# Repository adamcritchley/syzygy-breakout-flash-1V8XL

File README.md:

# Double-Wide SYZYGY Breakout Flash
SYZYGY 56 pin Breakout Board that uses smart VIO to support any voltage flash chip. I wanted a way to experiment with flash without having to spin a new board for each footprint or solder yet another BGA or TSOP. Flash programmers with ZIF adapters seemed like the best choice and SYZYGY would make it compatible with a wide range of FPGA boards. This is the biggest and baddest version of the other SYZYGY flash breakout boards and requires the smart VIO in the SYZYGY DNA to be set to your flash logic level. It requires two adjacent standard ports which can only be found on a handful of FPGA dev boards such as the [Opal Kelly XEM8320](https://opalkelly.com/products/xem8320/).

# Building Firmware
A prebuilt firmware has been provided in the 'firmware' directory. If you want to customize the SMART VIO then modify 'szg-flash-std.json' with the custom power values and use the official [SYZYGY tools](https://github.com/SYZYGYfpga/syzygy-tools/) repo to build the firmware. 

```bash
python ..\..\syzygy-tools\dna-tools\syzygy-tools.py -d ..\szg-dna\SZG-FLASH\szg-flash-std.json -f ..\..\syzygy-tools\pod-fw\avr-dna-fw-main.hex
```

# Fabrication
I used JLCPCB with 1oz inner and outer copper weight and the standard JLC041611-7628 impedance control.

# FPGA Development
The board has silkscreen pin designators for the Opal Kelly XEM8320. Theoretically you can use this board with any FPGA dev board that has a double-wide SYZYGY connector along with the respective controller for your flash device OR find someway to expose it to AXI and PS to use it with flashrom. As I figure out specific tools that work well then I'll update this README with tutorials.

# BOM
You can find datasheets for each component in the datasheets directory. All of the components can be bought from Mouser or Digikey. 
* Epson SG5032VAN (up to 100 MHz)
* Texas Instrument TLV1117LV
* Aries 48-6554-11
* KF2510 8-pin Vertical Connector

# Future Work
This board design is complete and tested with the Opal Kelly XEM8320. As I find/create IP and software that works with this board then I'll update this README with tutorials on how to use them. Feel free to create a GitHub issue detailing your own success story or use case.

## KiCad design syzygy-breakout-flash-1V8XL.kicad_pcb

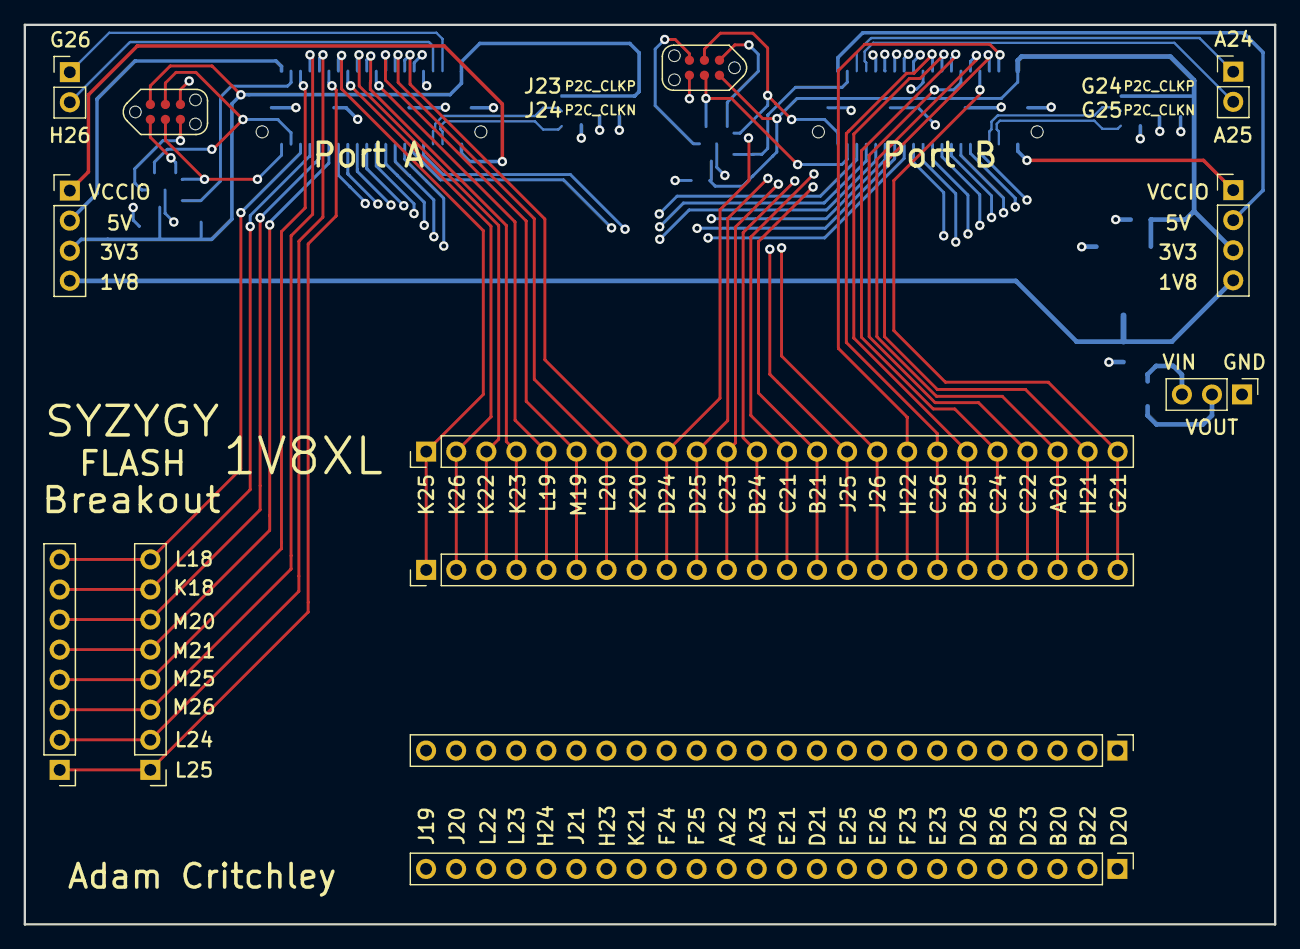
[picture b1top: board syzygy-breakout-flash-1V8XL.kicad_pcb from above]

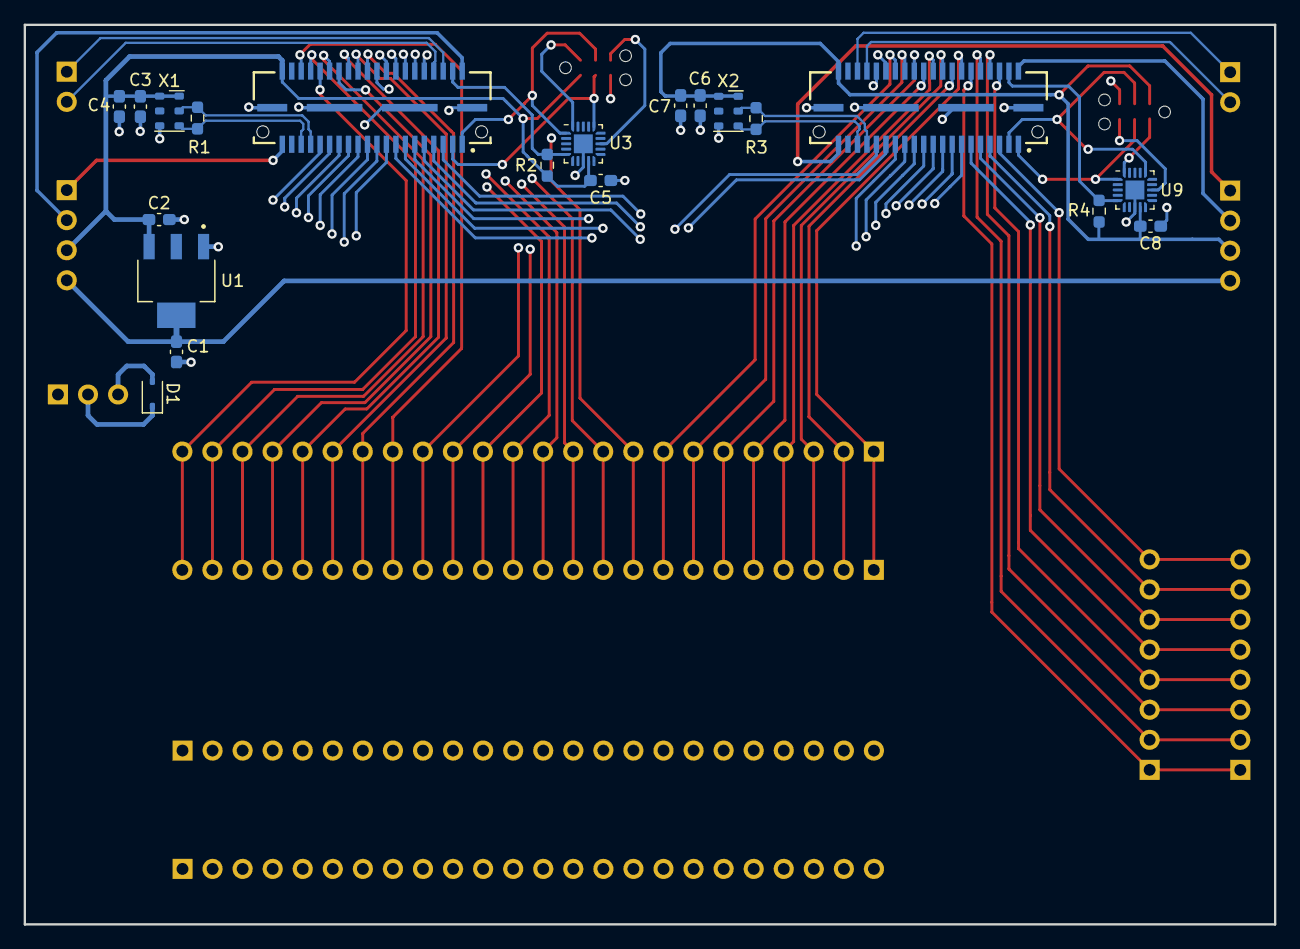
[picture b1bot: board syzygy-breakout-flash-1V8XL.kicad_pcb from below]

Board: 4 copper layers, 105.6 x 76.0 mm, 33 parts (20 on the bottom side), 81 nets.

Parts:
C1, C2, C3, C6: 1uF; C_0603_1608Metric_Pad1.08x0.95mm_HandSolder
C4, C5, C7, C8: 0.1uF; C_0603_1608Metric_Pad1.08x0.95mm_HandSolder
D1: BAT60AE6327HTSA1; D_SOD-323
J1, J2: QTE-020-01-F-D-A-TR; SAMTEC_QTE-020-01-F-D-A-TR
J3, J14: Conn_01x04; PinHeader_1x04_P2.54mm_Vertical
J4: Conn_01x03; PinHeader_1x03_P2.54mm_Vertical
J5, J7, J8, J9: Conn_01x24; PinHeader_1x24_P2.54mm_Vertical
J6, J10: TagConnect; TC2030-NL_SMALL
J11, J15: Conn_01x08; PinHeader_1x08_P2.54mm_Vertical
J12, J13: Conn_01x02; PinHeader_1x02_P2.54mm_Vertical
R1, R3: 100R; R_0603_1608Metric_Pad0.98x0.95mm_HandSolder
R2, R4: 10K; R_0603_1608Metric_Pad0.98x0.95mm_HandSolder
U1: TLV1117LV18DCYT; SOT230P700X180-4N
U3, U9: ATTINY44A-MMHR; QFN-20-1EP_3x3mm_P0.45mm_EP1.6x1.6mm
X1: SG3225VAN-100; Oscillator_SMD_Silicon_Labs_LGA-6_2.5x3.2mm_P1.25mm
X2: SG3225VAN-250; Oscillator_SMD_Silicon_Labs_LGA-6_2.5x3.2mm_P1.25mm

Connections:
+1V8: C1.1, J3.4, J14.4, U1.4 (VOUT)
+3V3: C2.2, C3.1, C4.1, C5.1, C6.1, C7.1, C8.1, J1.40 (+3.3V), J2.40 (+3.3V), J3.3, J6.2, J10.2, J14.3, R2.1, R4.1, U1.3 (IN), U3.9 (VCC), U9.9 (VCC), X1.1 (OE), X1.6 (Vcc), X2.1 (OE), X2.6 (Vcc)
+5V: J1.02 (+5V), J2.02 (+5V), J3.2, J14.2
/C2P_CLKN: J2.36 (C2P_CLKN), J5.17, J9.17
/C2P_CLKP: J2.34 (C2P_CLKP), J5.23, J9.23
/GPIO1: J2.06 (S1_D1P), J12.1
/GPIO2: J2.08 (S3_D1N), J12.2
/GPIO3: J1.34 (C2P_CLKP), J13.2
/GPIO4: J1.36 (C2P_CLKN), J13.1
/Peripheral MCU1/MISO: J10.1, U9.20 (PA5)
/Peripheral MCU1/~RESET: J10.5, U9.13 (~RESET/PB3)
/Peripheral MCU/MISO: J6.1, U3.20 (PA5)
/Peripheral MCU/~RESET: J6.5, U3.13 (~RESET/PB3)
/STD_P2C_CLKN: J2.35 (P2C_CLKN), R1.2, X1.4 (OUT)
/STD_P2C_CLKP: J2.33 (P2C_CLKP), R1.1, X1.5 (~OUT)
/STD_RGA: J2.04 (R_GA), R2.2, U3.5 (AREF/PA0)
/STD_SCL: J2.01 (SCL), J6.3, U3.1 (PA4)
/STD_SDA: J2.03 (SDA), J6.4, U3.16 (PA6)
/TXR_P2C_CLKN: J1.35 (P2C_CLKN), R3.2, X2.4 (OUT)
/TXR_P2C_CLKP: J1.33 (P2C_CLKP), R3.1, X2.5 (~OUT)
/TXR_RGA: J1.04 (R_GA), R4.2, U9.5 (AREF/PA0)
/TXR_SCL: J1.01 (SCL), J10.3, U9.1 (PA4)
/TXR_SDA: J1.03 (SDA), J10.4, U9.16 (PA6)
GND: C1.2, C2.1, C3.2, C4.2, C5.2, C6.2, C7.2, C8.2, J1.G1 (GND), J1.G2 (GND__1), J1.G3 (GND__2), J1.G4 (GND__3), J2.G1 (GND), J2.G2 (GND__1), J2.G3 (GND__2), J2.G4 (GND__3), J4.1, J6.6, J10.6, U1.1 (GND), U3.8 (GND), U3.21 (GND), U9.8 (GND), U9.21 (GND), X1.3 (GND), X2.3 (GND)
unnamed: D1.2 (A), J4.3
unnamed: J1.05 (S0_D0P), J11.8, J15.8
unnamed: J1.06 (S1_D1P), J11.4, J15.4
unnamed: J1.07 (S2_D0N), J11.7, J15.7
unnamed: J1.08 (S3_D1N), J11.3, J15.3
unnamed: J1.09 (S4_D2P), J11.6, J15.6
unnamed: J1.10 (S5_D3P), J11.2, J15.2
unnamed: J1.11 (S6_D2N), J11.5, J15.5
unnamed: J1.12 (S7_D3N), J11.1, J15.1
unnamed: J1.13 (S8_D4P), J7.24, J8.24
unnamed: J1.14 (S9_D5P), J5.1, J9.1
unnamed: J1.15 (S10_D4N), J7.23, J8.23
unnamed: J1.16 (S11_D5N), J5.2, J9.2
unnamed: J1.17 (S12_D6P), J7.22, J8.22
unnamed: J1.18 (S13_D7P), J5.3, J9.3
unnamed: J1.19 (S14_D6N), J7.21, J8.21
unnamed: J1.20 (S15_D7N), J5.4, J9.4
unnamed: J1.21 (S16), J7.20, J8.20
unnamed: J1.22 (S17), J5.5, J9.5
unnamed: J1.23 (S18), J7.19, J8.19
unnamed: J1.24 (S19), J5.6, J9.6
unnamed: J1.25 (S20), J7.18, J8.18
unnamed: J1.26 (S21), J5.7, J9.7
unnamed: J1.27 (S22), J7.17, J8.17
unnamed: J1.28 (S23), J5.8, J9.8
unnamed: J1.29 (S24), J7.16, J8.16
unnamed: J1.30 (S25), J5.16, J9.16
unnamed: J1.31 (S26), J7.15, J8.15
unnamed: J1.32 (S27), J5.15, J9.15
unnamed: J2.05 (S0_D0P), J7.14, J8.14
unnamed: J2.07 (S2_D0N), J7.13, J8.13
unnamed: J2.09 (S4_D2P), J7.12, J8.12
unnamed: J2.10 (S5_D3P), J5.9, J9.9
unnamed: J2.11 (S6_D2N), J7.11, J8.11
unnamed: J2.12 (S7_D3N), J5.10, J9.10
unnamed: J2.13 (S8_D4P), J7.10, J8.10
unnamed: J2.14 (S9_D5P), J5.11, J9.11
unnamed: J2.15 (S10_D4N), J7.9, J8.9
unnamed: J2.16 (S11_D5N), J5.12, J9.12
unnamed: J2.17 (S12_D6P), J7.8, J8.8
unnamed: J2.18 (S13_D7P), J5.13, J9.13
unnamed: J2.19 (S14_D6N), J7.7, J8.7
unnamed: J2.20 (S15_D7N), J5.14, J9.14
unnamed: J2.21 (S16), J7.6, J8.6
unnamed: J2.22 (S17), J5.18, J9.18
unnamed: J2.23 (S18), J7.5, J8.5
unnamed: J2.24 (S19), J5.19, J9.19
unnamed: J2.25 (S20), J7.4, J8.4
unnamed: J2.26 (S21), J5.20, J9.20
unnamed: J2.27 (S22), J7.3, J8.3
unnamed: J2.28 (S23), J5.21, J9.21
unnamed: J2.29 (S24), J7.2, J8.2
unnamed: J2.30 (S25), J5.22, J9.22
unnamed: J2.31 (S26), J7.1, J8.1
unnamed: J2.32 (S27), J5.24, J9.24
VCC: D1.1 (K), J4.2
VCCIO: J1.39 (VIO1), J2.39 (VIO1), J3.1, J14.1

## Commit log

2023-11-15 Clarified readme
2023-11-15 Clarified readme try 2
2023-11-30 feat(pcb): push latest verified pcb design
2023-12-10 Added BOM csv and part numbers to PCB
2023-12-26 added images
